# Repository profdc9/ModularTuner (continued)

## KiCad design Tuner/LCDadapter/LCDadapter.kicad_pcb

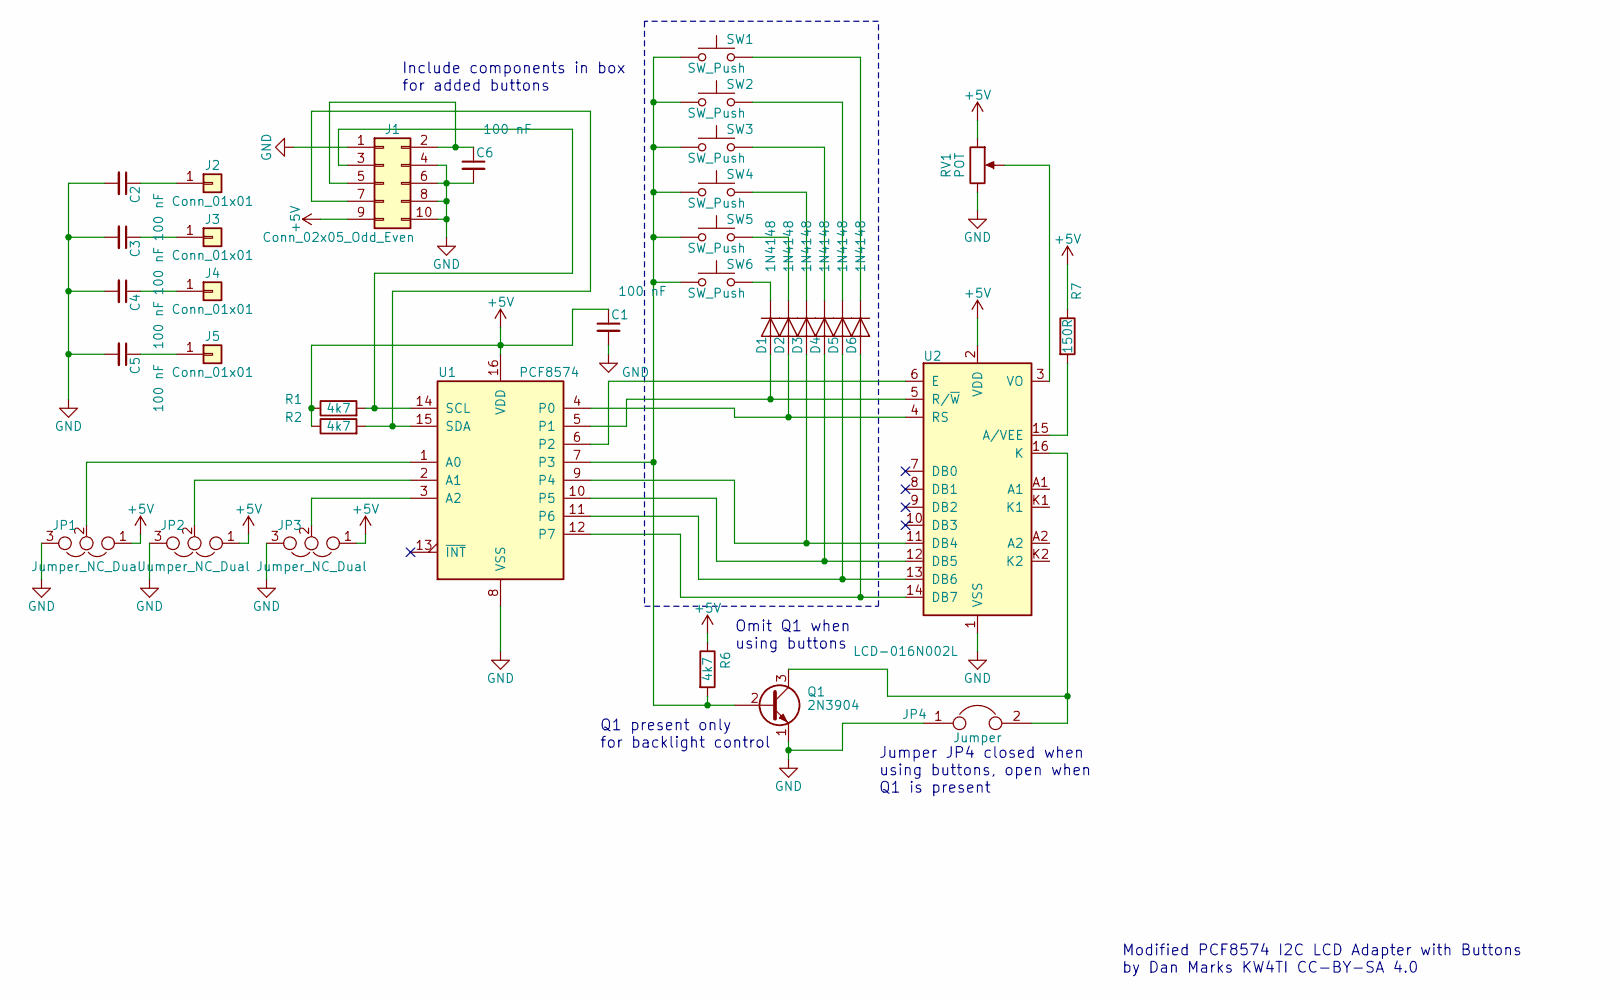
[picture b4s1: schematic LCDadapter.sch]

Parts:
C1, C2, C3, C4, C5, C6: 100 nF; C_Disc_D5.0mm_W2.5mm_P2.50mm
D1, D2, D3, D4, D5, D6: 1N4148; D_DO-35_SOD27_P7.62mm_Horizontal
J1: Conn_02x05_Odd_Even; Pin_Header_Straight_2x05_Pitch2.54mm
J2, J3, J4, J5: Conn_01x01; 1pin
JP1, JP2, JP3: Jumper_NC_Dual; Pin_Header_Straight_1x03_Pitch2.54mm
JP4: Jumper; Pin_Header_Straight_1x02_Pitch2.54mm
Q1: 2N3904; TO-92_Molded_Narrow
R1, R2, R6: 4k7; R_Axial_DIN0207_L6.3mm_D2.5mm_P7.62mm_Horizontal
R7: 150R; R_Axial_DIN0207_L6.3mm_D2.5mm_P7.62mm_Horizontal
RV1: POT; Potentiometer_Triwood_RM-065
SW1, SW2, SW3, SW4, SW5, SW6: SW_Push; SW_PUSH_6mm_h4.3mm
U1: PCF8574; DIP-16_W7.62mm_Socket
U2: LCD-016N002L; Pin_Header_Straight_1x16_Pitch2.54mm

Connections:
+5V: C1.1, J1.9, JP1.1, JP2.1, JP3.1, R1.1, R2.1, R6.1, R7.1, RV1.1, U1.16 (VDD), U2.2 (VDD)
GND: C1.2, C2.2, C3.2, C4.2, C5.2, C6.2, J1.1, J1.4, J1.6, J1.8, J1.10, JP1.3, JP2.3, JP3.3, JP4.1, Q1.1 (E), RV1.3, U1.8 (VSS), U2.1 (VSS)
unnamed: C2.1, J2.1
unnamed: C3.1, J3.1
unnamed: C4.1, J4.1
unnamed: C5.1, J5.1
unnamed: C6.1, J1.2, J1.5
unnamed: D1.1 (K), SW6.2
unnamed: D1.2 (A), U1.5 (P1), U2.5 (R/~W)
unnamed: D2.1 (K), SW5.2
unnamed: D2.2 (A), U1.4 (P0), U2.4 (RS)
unnamed: D3.1 (K), SW4.2
unnamed: D3.2 (A), U1.9 (P4), U2.11 (DB4)
unnamed: D4.1 (K), SW3.2
unnamed: D4.2 (A), U1.10 (P5), U2.12 (DB5)
unnamed: D5.1 (K), SW2.2
unnamed: D5.2 (A), U1.11 (P6), U2.13 (DB6)
unnamed: D6.1 (K), SW1.2
unnamed: D6.2 (A), U1.12 (P7), U2.14 (DB7)
unnamed: J1.3, R1.2, U1.14 (SCL)
unnamed: J1.7, R2.2, U1.15 (SDA)
unnamed: JP1.2, U1.1 (A0)
unnamed: JP2.2, U1.2 (A1)
unnamed: JP3.2, U1.3 (A2)
unnamed: JP4.2, Q1.3 (C), U2.16 (K)
unnamed: Q1.2 (B), R6.2, SW1.1, SW2.1, SW3.1, SW4.1, SW5.1, SW6.1, U1.7 (P3)
unnamed: R7.2, U2.15 (A/VEE)
unnamed: RV1.2, U2.3 (VO)
unnamed: U1.6 (P2), U2.6 (E)

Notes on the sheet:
Modified PCF8574 I2C LCD Adapter with Buttons by Dan Marks KW4TI CC-BY-SA 4.0
Omit Q1 when using buttons
Jumper JP4 closed when using buttons, open when Q1 is present
Q1 present only for backlight control
Include components in box for added buttons

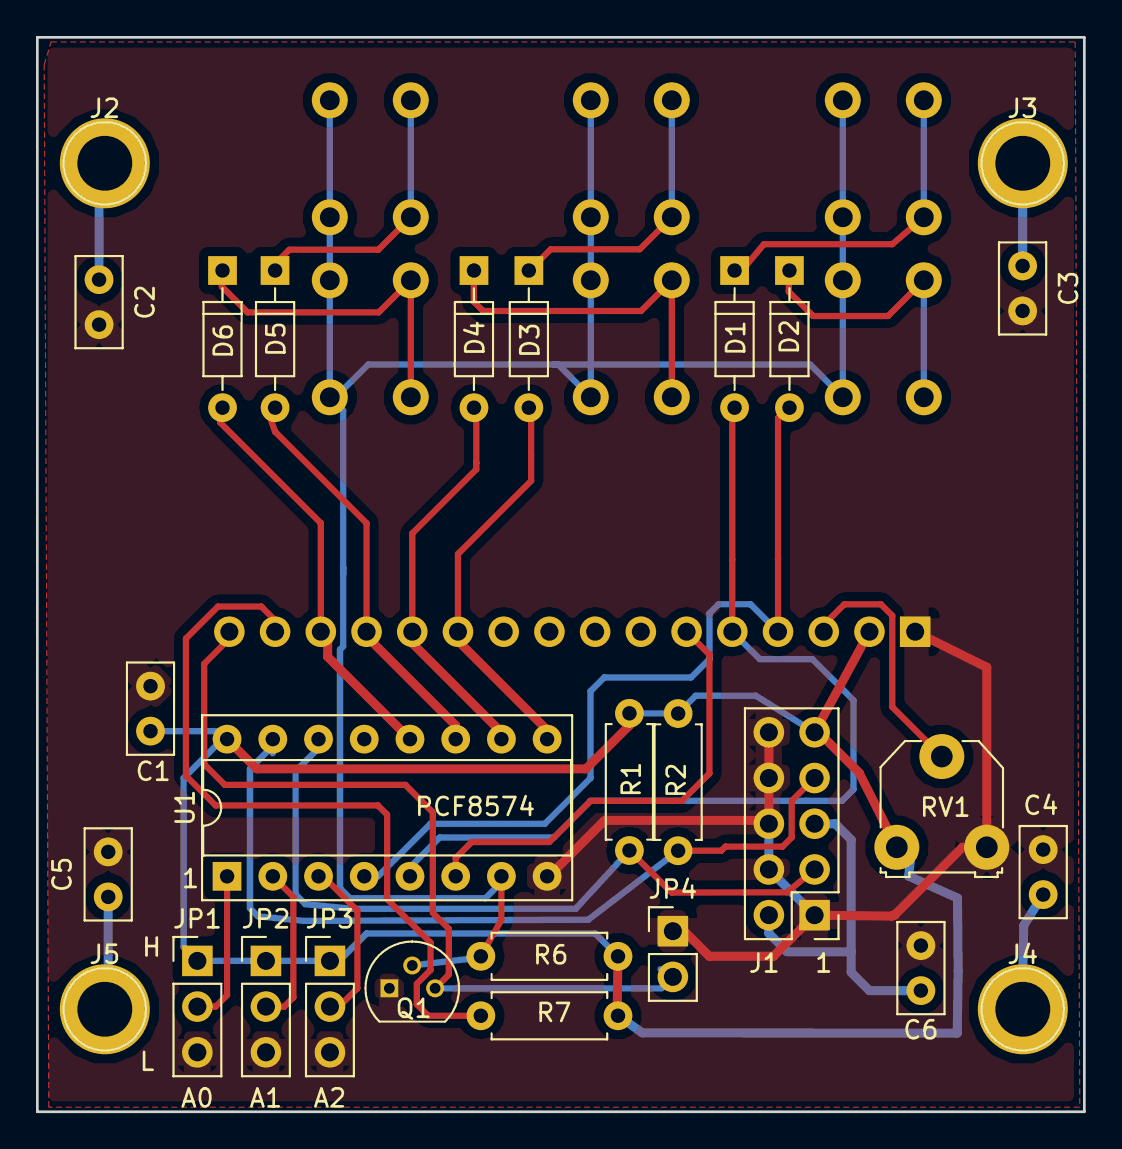
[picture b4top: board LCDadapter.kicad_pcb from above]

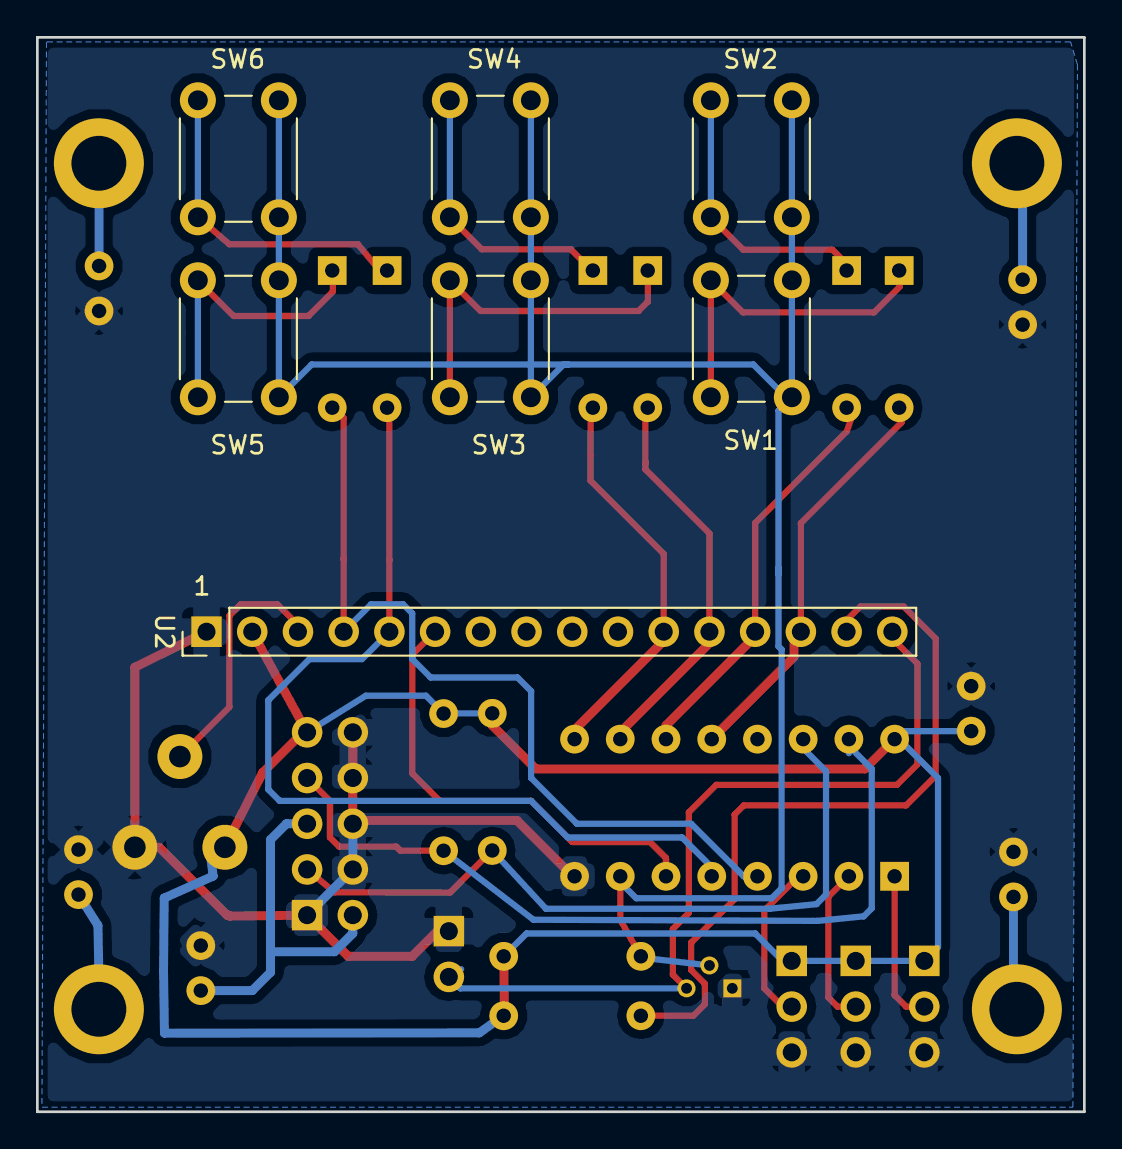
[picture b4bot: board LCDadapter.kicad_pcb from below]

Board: 2 copper layers, 58.2 x 59.7 mm, 35 parts (7 on the bottom side), 29 nets.

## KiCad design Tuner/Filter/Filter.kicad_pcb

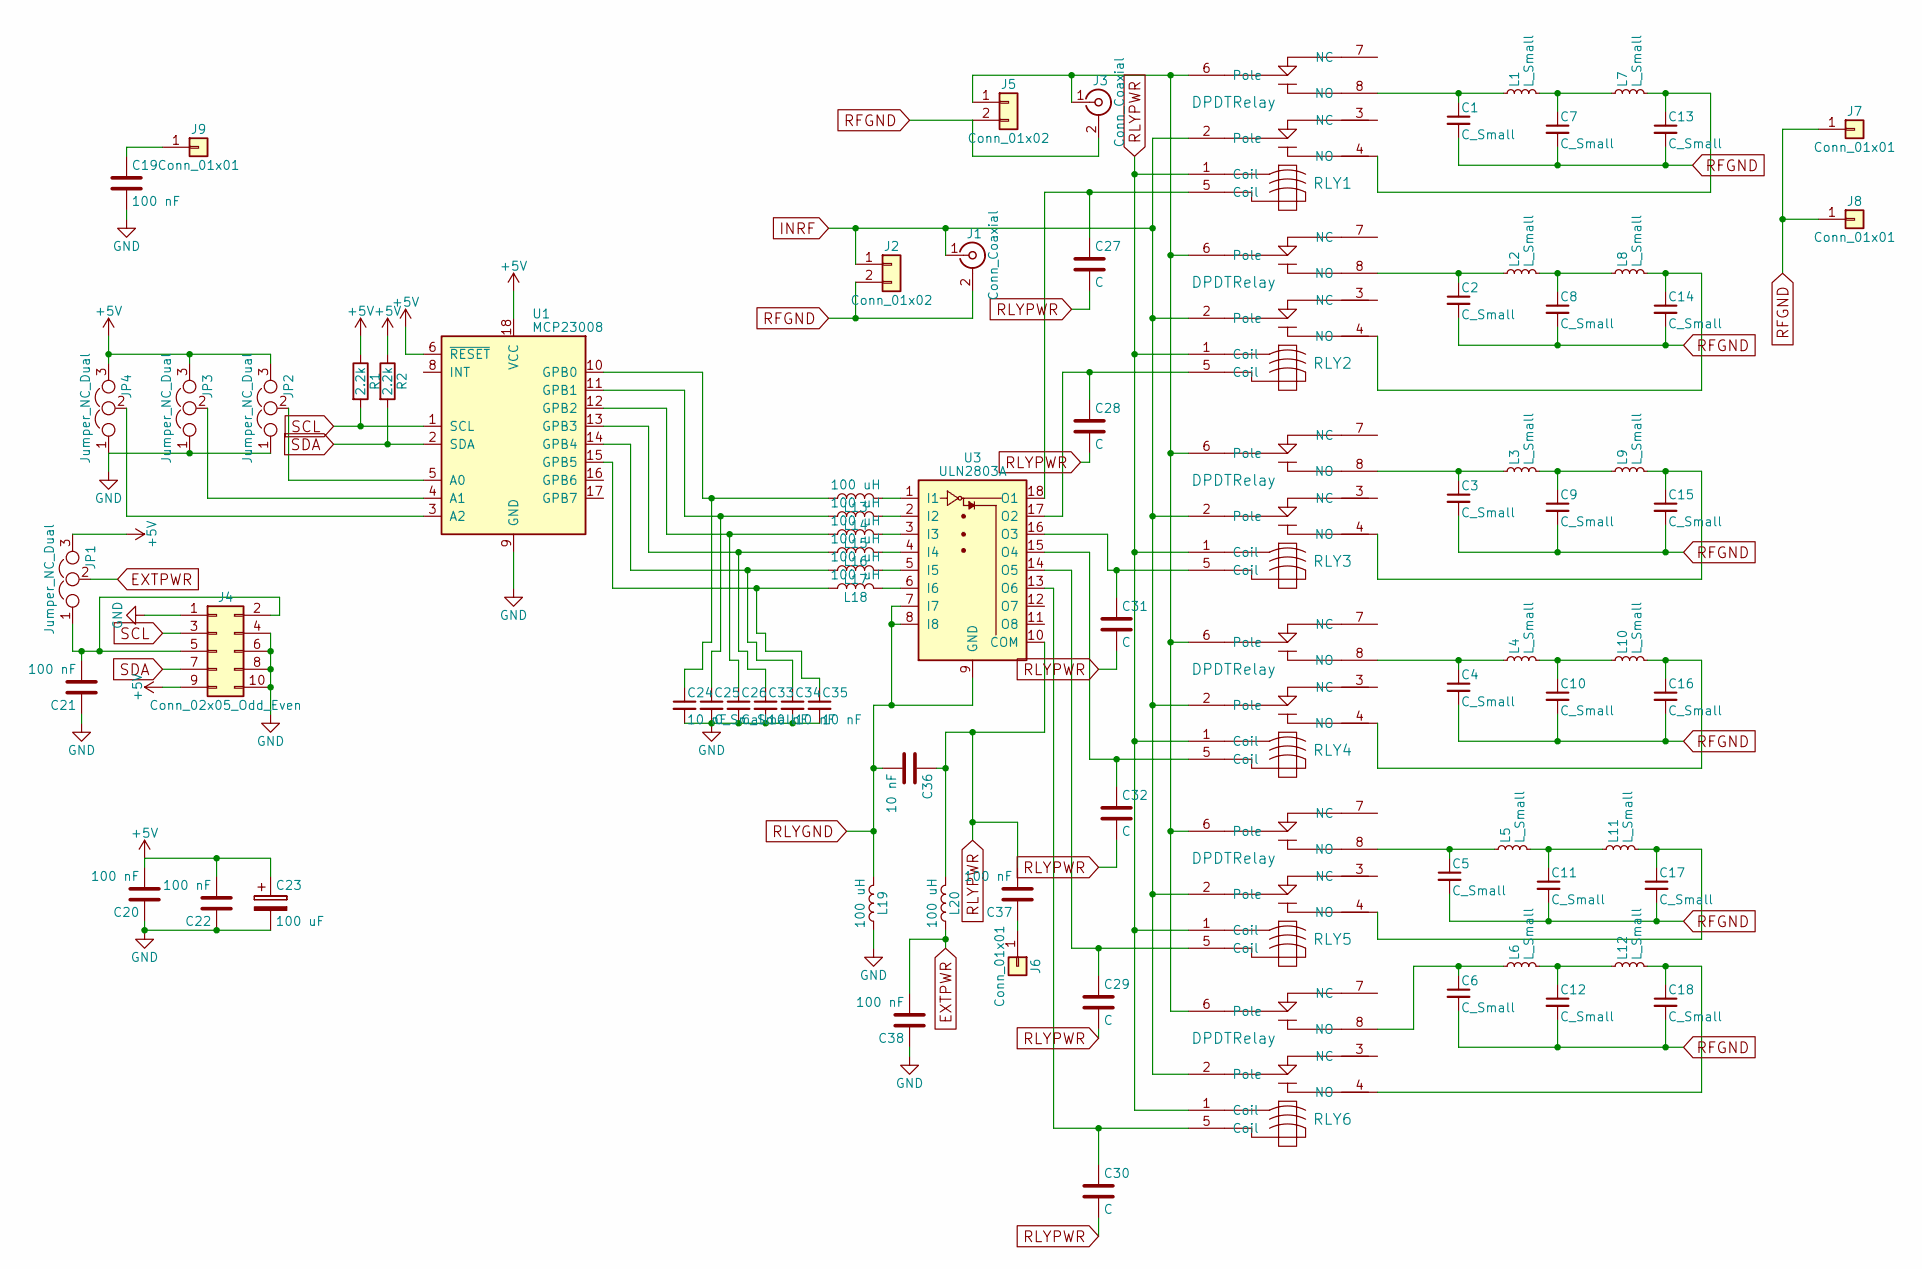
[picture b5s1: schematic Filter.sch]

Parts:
C1, C2, C3, C4, C5, C6, C7, C8, C9, C10, C11, C12, C13, C14, C15, C16, C17, C18: C_Small; C_Disc_SMD
C19, C20, C21, C22, C37, C38: 100 nF; C_Disc_D5.0mm_W2.5mm_P2.50mm
C23: 100 uF; CP_Radial_D6.3mm_P2.50mm
C24, C33, C34, C35: 10 nF; C_Disc_D5.0mm_W2.5mm_P2.50mm
C25, C26: C_Small; C_Disc_D5.0mm_W2.5mm_P2.50mm
C27, C28, C29, C30, C31, C32: C; C_Disc_D5.0mm_W2.5mm_P2.50mm
C36: 10 nF; C_Disc_D5.0mm_W2.5mm_P5.00mm
J1, J3: Conn_Coaxial; bnc_90_1-1337543-0
J2, J5: Conn_01x02; TerminalBlock_bornier-2_P5.08mm
J4: Conn_02x05_Odd_Even; Pin_Header_Straight_2x05_Pitch2.54mm
J6, J7, J8, J9: Conn_01x01; 1pin
JP1, JP2, JP3, JP4: Jumper_NC_Dual; Pin_Header_Straight_1x03_Pitch2.54mm
L1, L2, L3, L4, L5, L6, L7, L8, L9, L10, L11, L12: L_Small; L_Toroid_Vertical_L13.0mm_W6.5mm_P5.60mm
L13, L14, L15, L16, L17, L18, L19, L20: 100 uH; L_Axial_L5.3mm_D2.2mm_P7.62mm_Horizontal_Vishay_IM-1
R1, R2: 2.2k; R_Axial_DIN0207_L6.3mm_D2.5mm_P7.62mm_Horizontal
RLY1, RLY2, RLY3, RLY4, RLY5, RLY6: DPDTRelay; G2VRelay
U1: MCP23008; DIP-18_W7.62mm_Socket
U3: ULN2803A; DIP-18_W7.62mm_Socket

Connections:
+5V: C20.2, C22.2, C23.1, J4.9, JP1.3, JP2.3, JP3.3, JP4.3, R1.1, R2.1, U1.6 (~RESET), U1.18 (VCC)
EXTPWR: C38.2, JP1.2, L20.1
GND: C19.2, C20.1, C21.1, C22.1, C23.2, C24.2, C25.2, C26.2, C33.2, C34.2, C35.2, C38.1, J4.1, J4.4, J4.6, J4.8, J4.10, JP2.1, JP3.1, JP4.1, L19.1, U1.9 (GND)
INRF: J1.1 (In), J2.1, RLY1.2 (Pole), RLY2.2 (Pole), RLY3.2 (Pole), RLY4.2 (Pole), RLY5.2 (Pole), RLY6.2 (Pole)
unnamed: C1.1, L1.1, RLY1.8 (NO)
unnamed: C2.1, L2.1, RLY2.8 (NO)
unnamed: C3.1, L3.1, RLY3.8 (NO)
unnamed: C4.1, L4.1, RLY4.8 (NO)
unnamed: C5.1, L5.1, RLY5.8 (NO)
unnamed: C6.1, L6.1, RLY6.8 (NO)
unnamed: C7.1, L1.2, L7.1
unnamed: C8.1, L2.2, L8.1
unnamed: C9.1, L3.2, L9.1
unnamed: C10.1, L4.2, L10.1
unnamed: C11.1, L5.2, L11.1
unnamed: C12.1, L6.2, L12.1
unnamed: C13.1, L7.2, RLY1.4 (NO)
unnamed: C14.1, L8.2, RLY2.4 (NO)
unnamed: C15.1, L9.2, RLY3.4 (NO)
unnamed: C16.1, L10.2, RLY4.4 (NO)
unnamed: C17.1, L11.2, RLY5.4 (NO)
unnamed: C18.1, L12.2, RLY6.4 (NO)
unnamed: C19.1, J9.1
unnamed: C21.2, J4.2, J4.5, JP1.1
unnamed: C24.1, L13.1, U1.10 (GPB0)
unnamed: C25.1, L14.1, U1.11 (GPB1)
unnamed: C26.1, L15.1, U1.12 (GPB2)
unnamed: C27.1, RLY1.5 (Coil), U3.18 (O1)
unnamed: C28.1, RLY2.5 (Coil), U3.17 (O2)
unnamed: C29.1, RLY5.5 (Coil), U3.14 (O5)
unnamed: C30.1, RLY6.5 (Coil), U3.13 (O6)
unnamed: C31.1, RLY3.5 (Coil), U3.16 (O3)
unnamed: C32.1, RLY4.5 (Coil), U3.15 (O4)
unnamed: C33.1, L16.1, U1.13 (GPB3)
unnamed: C34.1, L17.1, U1.14 (GPB4)
unnamed: C35.1, L18.1, U1.15 (GPB5)
unnamed: C37.1, J6.1
unnamed: J3.1 (In), J5.1, RLY1.6 (Pole), RLY2.6 (Pole), RLY3.6 (Pole), RLY4.6 (Pole), RLY5.6 (Pole), RLY6.6 (Pole)
unnamed: JP2.2, U1.5 (A0)
unnamed: JP3.2, U1.4 (A1)
unnamed: JP4.2, U1.3 (A2)
unnamed: L13.2, U3.1 (I1)
unnamed: L14.2, U3.2 (I2)
unnamed: L15.2, U3.3 (I3)
unnamed: L16.2, U3.4 (I4)
unnamed: L17.2, U3.5 (I5)
unnamed: L18.2, U3.6 (I6)
RFGND: C1.2, C2.2, C3.2, C4.2, C5.2, C6.2, C7.2, C8.2, C9.2, C10.2, C11.2, C12.2, C13.2, C14.2, C15.2, C16.2, C17.2, C18.2, J1.2 (Ext), J2.2, J3.2 (Ext), J5.2, J7.1, J8.1
RLYGND: C36.2, L19.2, U3.7 (I7), U3.8 (I8), U3.9 (GND)
RLYPWR: C27.2, C28.2, C29.2, C30.2, C31.2, C32.2, C36.1, C37.2, L20.2, RLY1.1 (Coil), RLY2.1 (Coil), RLY3.1 (Coil), RLY4.1 (Coil), RLY5.1 (Coil), RLY6.1 (Coil), U3.10 (COM)
SCL: J4.3, R1.2, U1.1 (SCL)
SDA: J4.7, R2.2, U1.2 (SDA)

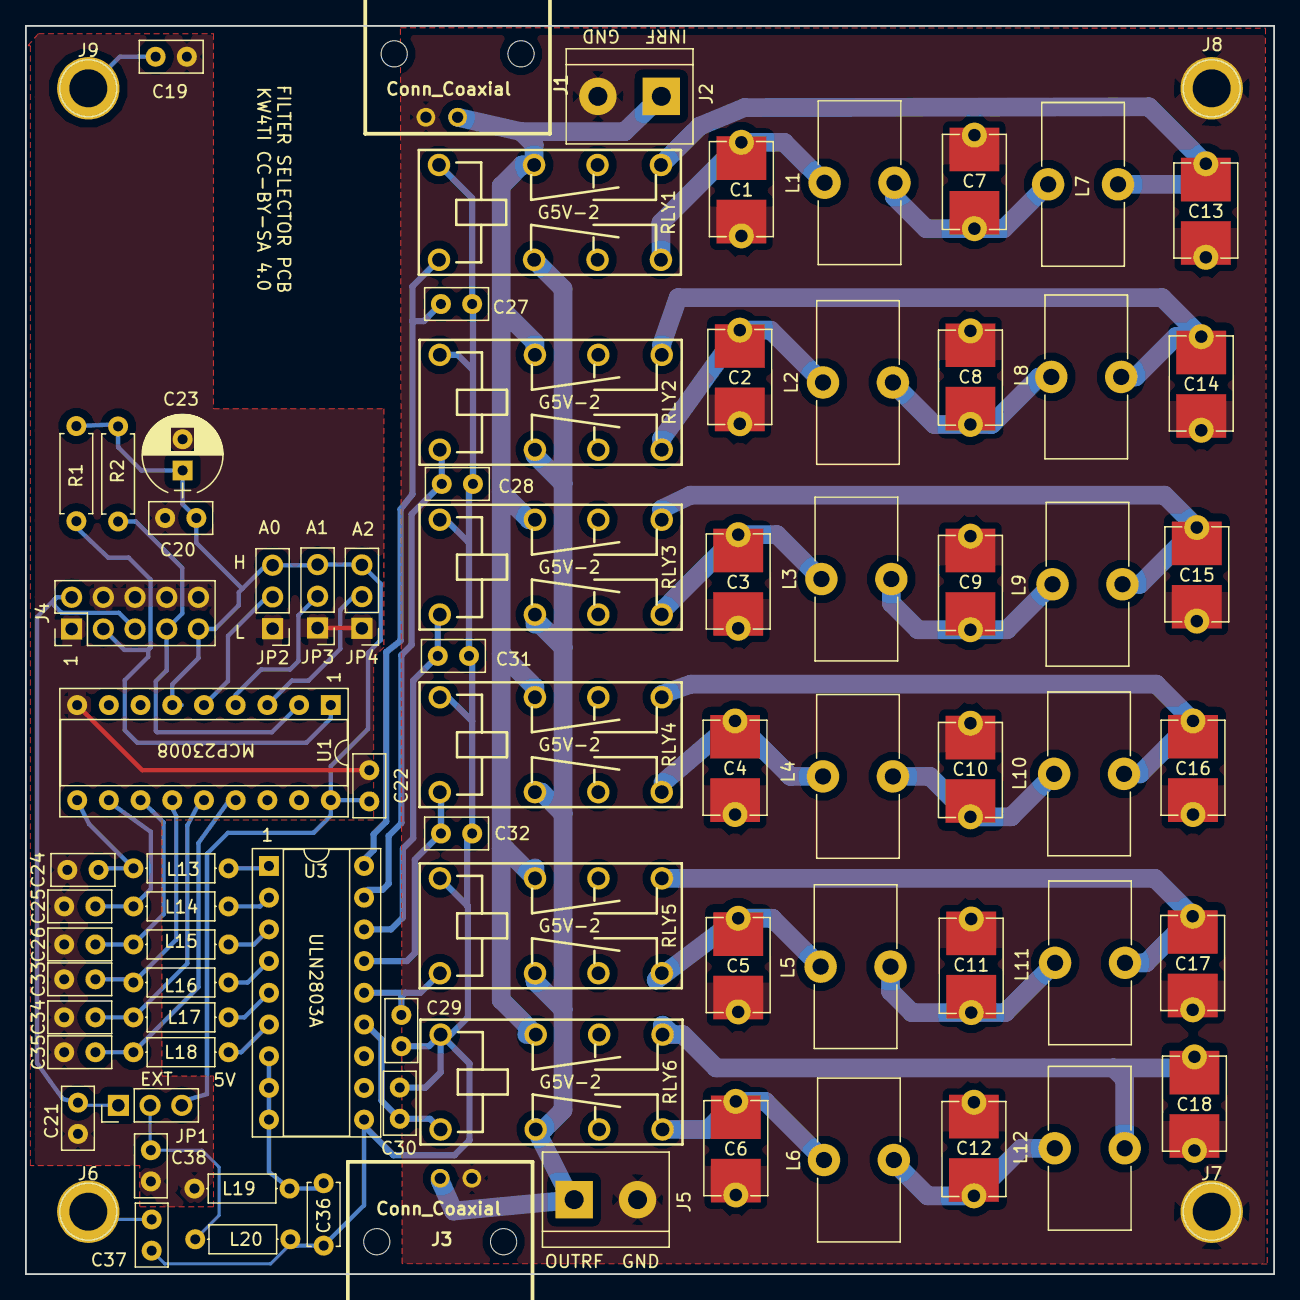
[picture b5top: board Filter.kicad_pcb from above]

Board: 2 copper layers, 100.0 x 100.0 mm, 81 parts (0 on the bottom side), 52 nets.

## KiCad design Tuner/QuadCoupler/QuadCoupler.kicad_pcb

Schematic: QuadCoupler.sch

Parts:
C1, C2, C3, C4, C14, C19: 10 nF; C_Disc_D5.0mm_W2.5mm_P5.00mm
C5, C6, C7, C11, C12, C13, C15, C18, C21, C23, C27, C28, C29: NC; C_Disc_D5.0mm_W2.5mm_P5.00mm
C8, C31: 68 pF 1 kV; C_Disc_D5.0mm_W2.5mm_P5.00mm
C9, C10, C30, C32: 47 pF 1 kV; C_Disc_D5.0mm_W2.5mm_P5.00mm
C16, C17, C20, C22, C24, C25, C26: 10 nF 1 kV; C_Disc_D5.0mm_W2.5mm_P5.00mm
D1, D2, D3, D4, D5, D6, D7, D8: 1N4148; D_DO-35_SOD27_P7.62mm_Horizontal
J1, J7, J8, J9, J11, J12, J13, J14, J15, J16, J17, J21, J22, J23, J24: Conn_01x01; 1pin
J2, J3, J4, J5, J6: Conn_Coaxial; bnc_90_1-1337543-0_pad_combo
J10, J19: Conn_01x02; TerminalBlock_bornier-2_P5.08mm
JP1, JP2, JP3, JP4, JP5, JP6, JP7, JP8, JP9, JP10: Jumper_NC_Small; Pin_Header_Straight_1x02_Pitch2.54mm
R1, R2, R3, R4, R5, R6, R9, R10, R11, R12, R13, R14, R21, R22, R23, R24, R25, R26, R27, R28, R29, R30, R31, R32, R33, R34, R35, R36, R37, R38: 1k; R_Axial_DIN0411_L9.9mm_D3.6mm_P12.70mm_Horizontal
R7, R16, R18, R19: 100k; R_Axial_DIN0207_L6.3mm_D2.5mm_P7.62mm_Horizontal
R8, R15, R17, R20: 10k; R_Axial_DIN0207_L6.3mm_D2.5mm_P7.62mm_Horizontal
TR1, TR2, TR3, TR4, TR5, TR6: autotransformer

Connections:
GND: C1.2, C2.2, C3.2, C4.2, C5.2, C6.2, C7.2, C8.2, C9.2, C10.2, C14.2, C19.2, C27.2, C28.2, C29.2, C30.2, C31.2, C32.2, J2.2 (Ext), J3.2 (Ext), J4.2 (Ext), J5.2 (Ext), J6.2 (Ext), J10.2, J12.1, J14.1, J19.2, J21.1, J22.1, J23.1, J24.1, JP1.2, JP2.2, JP7.2, JP8.2, R8.1, R15.1, R17.1, R20.1, TR1.1, TR3.1, TR4.1
unnamed: C1.1, JP1.1, R15.2, R18.1
unnamed: C2.1, JP2.1, R16.1, R17.2
unnamed: C3.1, JP7.1, R7.1, R8.2
unnamed: C4.1, JP8.1, R19.1, R20.2
unnamed: C10.1, C30.1, TR4.2, TR6.2
unnamed: C6.1, C11.1, C28.1, JP3.1, R1.1, R2.1, R3.1, R4.1, R27.1, R28.1, R29.1, R30.1, R31.1, R32.1, TR2.3, TR4.3
unnamed: C5.1, C11.2, C27.1, JP10.2, R1.2, R2.2, R3.2, R4.2, R27.2, R28.2, R29.2, R30.2, R31.2, R32.2, TR2.1, TR3.3
unnamed: C12.1, C18.2, C23.2, JP5.1, R5.1, R9.1, R11.1, R13.1, R21.1, R22.1, R23.1, R24.1, R25.1, R26.1, TR5.3
unnamed: C12.2, C16.2, C22.2, JP9.1, R5.2, R9.2, R11.2, R13.2, R21.2, R22.2, R23.2, R24.2, R25.2, R26.2, TR5.1
unnamed: C13.1, C17.2, C20.2, JP6.2, R6.1, R10.1, R12.1, R14.1, R33.1, R34.1, R35.1, R36.1, R37.1, R38.1, TR6.3
unnamed: C13.2, C15.2, C21.2, JP4.2, R6.2, R10.2, R12.2, R14.2, R33.2, R34.2, R35.2, R36.2, R37.2, R38.2, TR6.1
unnamed: C14.1, C19.1, J1.1, J7.1, J8.1, J9.1, J10.1, J19.1
unnamed: C15.1, C21.1, J4.1 (In), J17.1
unnamed: C16.1, C22.1, J6.1 (In), J15.1
unnamed: C17.1, C20.1, J2.1 (In), J11.1
unnamed: C18.1, C23.1, J5.1 (In), J13.1
unnamed: C7.1, C24.1, C25.1, C26.1, C29.1, TR1.3
unnamed: C24.2, C25.2, C26.2, J3.1 (In), J16.1
unnamed: C8.1, C31.1, TR1.2, TR2.2
unnamed: C9.1, C32.1, TR3.2, TR5.2
unnamed: D1.1 (K), D4.2 (A)
unnamed: D1.2 (A), JP3.2, JP6.1
unnamed: D2.1 (K), D7.2 (A)
unnamed: D2.2 (A), JP5.2
unnamed: D3.1 (K), D5.2 (A)
unnamed: D3.2 (A), JP4.1
unnamed: D4.1 (K), R18.2
unnamed: D5.1 (K), R16.2
unnamed: D6.1 (K), D8.2 (A)
unnamed: D6.2 (A), JP9.2, JP10.1
unnamed: D7.1 (K), R7.2
unnamed: D8.1 (K), R19.2

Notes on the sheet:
1:1 bifilar autotransformer
14:10 P3:P2 trifilar 1.96:1 impedance autotransformer 5 turns of trifilar wire on two FT82-43 cores, the final turn removed
QUAD POWER COUPLER BY DAN MARKS KW4TI CC-BY-SA 4.0

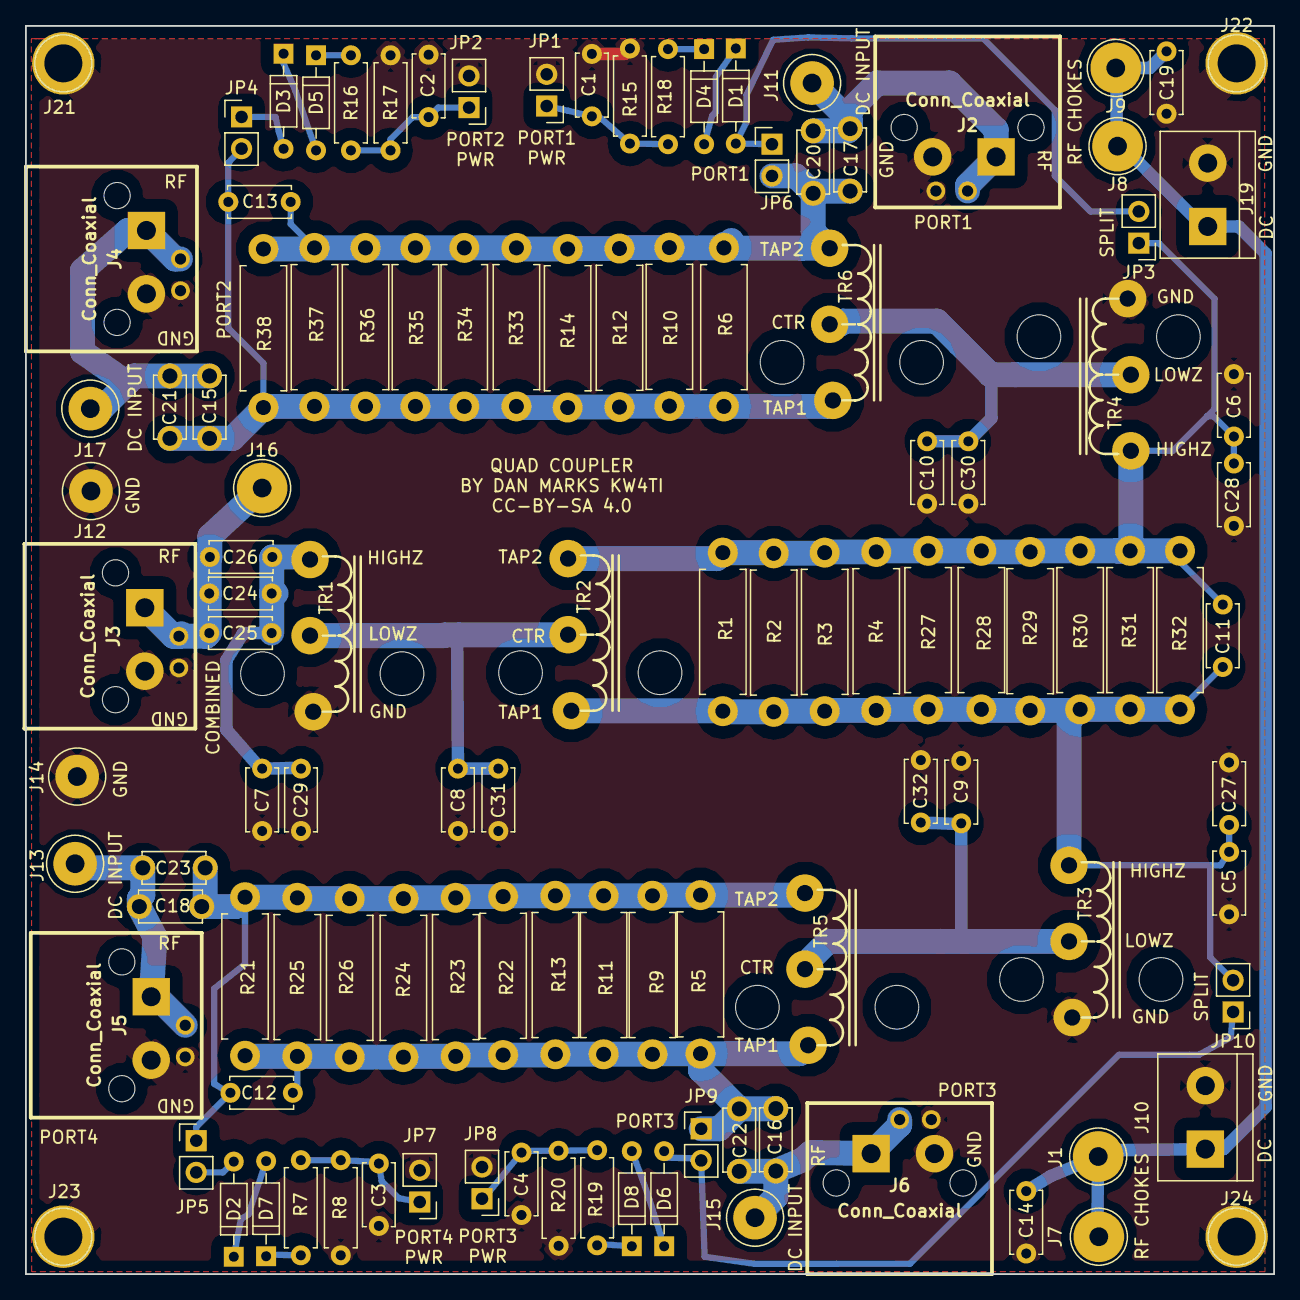
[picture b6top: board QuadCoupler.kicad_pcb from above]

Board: 2 copper layers, 100.0 x 100.0 mm, 116 parts (0 on the bottom side), 33 nets.

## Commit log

2018-08-24 added Bill of Materials
2018-09-01 Added separate relay and relay control board
2018-09-02 added PDFs and PNGs to Relay/RelayControl
2018-09-03 Added RF Shielding to ReversibleSection
2018-09-03 A few more vias on the ReversibleSection
2018-09-10 Modified RelayControl and Reversible Section to Isolate Digital from Analog sections using RF chokes
2018-09-11 Added extra filtering and shunt to RF ground
2018-09-15 JLCPCB submitted RelayControl version
2018-09-23 JLCPCB order 09232018 - improved grounding - improved I2C cabling - NEO7M port - support for common mode chokes - relay board now has capacitors on all coils
2018-10-07 Relay boards changed to have coil terminals all on same side
2018-10-22 Added boards for SMIH/Schrack Relays
2018-10-23 Added HK19F boards
2018-10-24 Error in pinout HK19F fixed
2018-11-01 JLCPCB Nov 1 2018
2018-11-20 First code commit
2018-12-20 Got rid of two non-working boards
2019-02-16 Moved some grounds around
2019-02-18 Tandem Match PCB added
2019-02-18 TandemMatch to JLCPCB
2019-02-21 Fixed TandemMatch grounding problem
2019-02-24 Added new DelayLine board, modified TandemMatch
2019-02-24 Added phase reversal transformer
2019-02-24 Added Quad Coupler
2019-02-24 Modified DelayLine to include bypass control
2019-02-25 Changed DelayLine to short out sections
2019-02-25 Stupid mistake, went to another method
2019-02-25 Added LittleDelayLine
2019-02-27 Added more instrumentation to TandemMatch, fixed grounding issue
2019-03-02 Removed 1k resistors, did some more rearranging on TandemMatch
2019-03-03 Added BNC and screw terminal combo pads
2019-03-04 Changed over yet more to BNC
2019-03-05 TandenMatch now has DC-RF bias tee
2019-03-06 Modified connectors on Reversible boards
2019-03-07 Symmetrized QuadCoupler Layout
2019-03-08 A few tweaks
2019-03-10 Actually tuning code now!
2019-03-12 Put level shifters into controller
2019-03-13 Changed bypass method on delay lines
2019-03-14 Added configuration structures and tuner status
2019-03-15 Programmable switch order to search for tuning
2019-03-15 Added autosave
2019-03-17 Changed I2C cable pinoutgit add Tunergit add Tuner Also added ICOM rig support
2019-03-18 Added icom tuner abort and other features
2019-03-19 Fixed icom tuning bad tuning report
2019-03-20 Fixed spacing between BNC connectors in Delay Lines
2019-03-22 Made PCF8574 LCD adapter with buttons
2019-03-23 Added some initial I2C user interface stuff
2019-03-23 Did not commit actual version of Liquidcrystal I2C with buttons
2019-03-26 JLCPCB order 2019-03-25
2019-03-27 Added nonswitched output to ReversibleSections
2019-03-30 Change named to DirectionalCoupler, fixed order of two pins in QuadCoupler
2019-04-03 Added SwitchBus
2019-04-06 Documentation update
2019-04-08 Added LittleSwitchBus and RelayBreakout
2019-04-09 Added Bill of Materials to PCBs
2019-04-13 Added OptoisolatedRelay
2019-04-13 Added LEDs to OptoisolatedRelay
2019-04-16 Added some fixes to tuner code
2019-05-23 Some modifications to Quadcoupler for easier access
2019-07-03 Added switchable low pass filter PCB
2019-08-23 LCDAdapter added dual polarity set I2C address
2019-10-16 Moved digital signal interface connector over
2019-10-18 Changed resistor values for termination
2019-10-26 Changed the way the tuning is done so that the bypass is automatically selected when zero inductance is needed
2019-10-26 Added firmware file
2019-11-24 QRO Tuning Unit Added
2019-11-24 Changed capacitance high-Z low-Z to have less series inductance
2019-11-25 Added extra capacitors between relay power and ground posts
2019-11-25 Added extra capacitors to ground to large relay boards
2019-11-25 Missed the gerbers for DelayLine
2019-11-25 Changed some of the capacitors to NC becaue they might cause problems in some situations
2019-11-29 Added extra mounting holes to ground ReversibleLittleSection
2019-11-30 Changed from 2x12 IDC to more common 2x13 IDC
2019-12-04 Added yet more ground connections
